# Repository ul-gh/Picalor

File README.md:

# Picalor

## Multi-Channel Heat Balance Calorimetry on the Raspberry Pi
--> Incomplete - work-in-progress! <--

Thermal power (or heat flow) measurement of one segmented or multiple
individual liquid-cooled or liquid-heated systems under the assumption
that the enthalpy difference of the fluid entering and exiting each system
per unit of time is equal to the energy dissipated or released by the system.

Quasi-isothermal condition can be achieved by using a sufficiently high
flow rate. Accurate heat flow measurements under these conditions
require very sensitive and robust differential temperature sensing.

This is implemented by the Picalor hardware using platinum resistive
temperature sensors in a deflection-type bridge configuration connected
to a multi-channel, high-precision delta-sigma ADC system.

When performing the measurement with fluid temperatures set nearly at
environmental temperature level, convection and radiation heat loss
can be made negligible e.g. for power loss measurements in electronics.

For applications in chemistry, the multi-channel hardware can be useful
for Constant Flux Calorimetry or segmented Continuous Reaction Calorimters.

Supported hardware:

* Picalor OSHW Raspberry Pi add-on circuit board featuring:
    - 16-channel analog frontend for Pt 1000 sensors
    - 4x pulse-timing flow sensor inputs
    - 2x ADS1256 24-Bit 8-ch ADC
* Waveshare "High Precision AD/DA board"

## Hardware:

* PCB Design Files: [picalor_hardware](picalor_hardware/)
* [Circuit Diagram (PDF)](https://ul-gh.github.io/Picalor/picalor_hardware/picalor_pcb.pdf)
* [Circuit BOM (HTML)](https://ul-gh.github.io/Picalor/picalor_hardware/ibom.html)

## Software Documentation (Generated):
* [Picalor Core (server component)](https://ul-gh.github.io/Picalor/picalor_core/html/namespaces.html)
* [Picalor App (browser client)](https://ul-gh.github.io/Picalor/picalor_app/html/files.html)

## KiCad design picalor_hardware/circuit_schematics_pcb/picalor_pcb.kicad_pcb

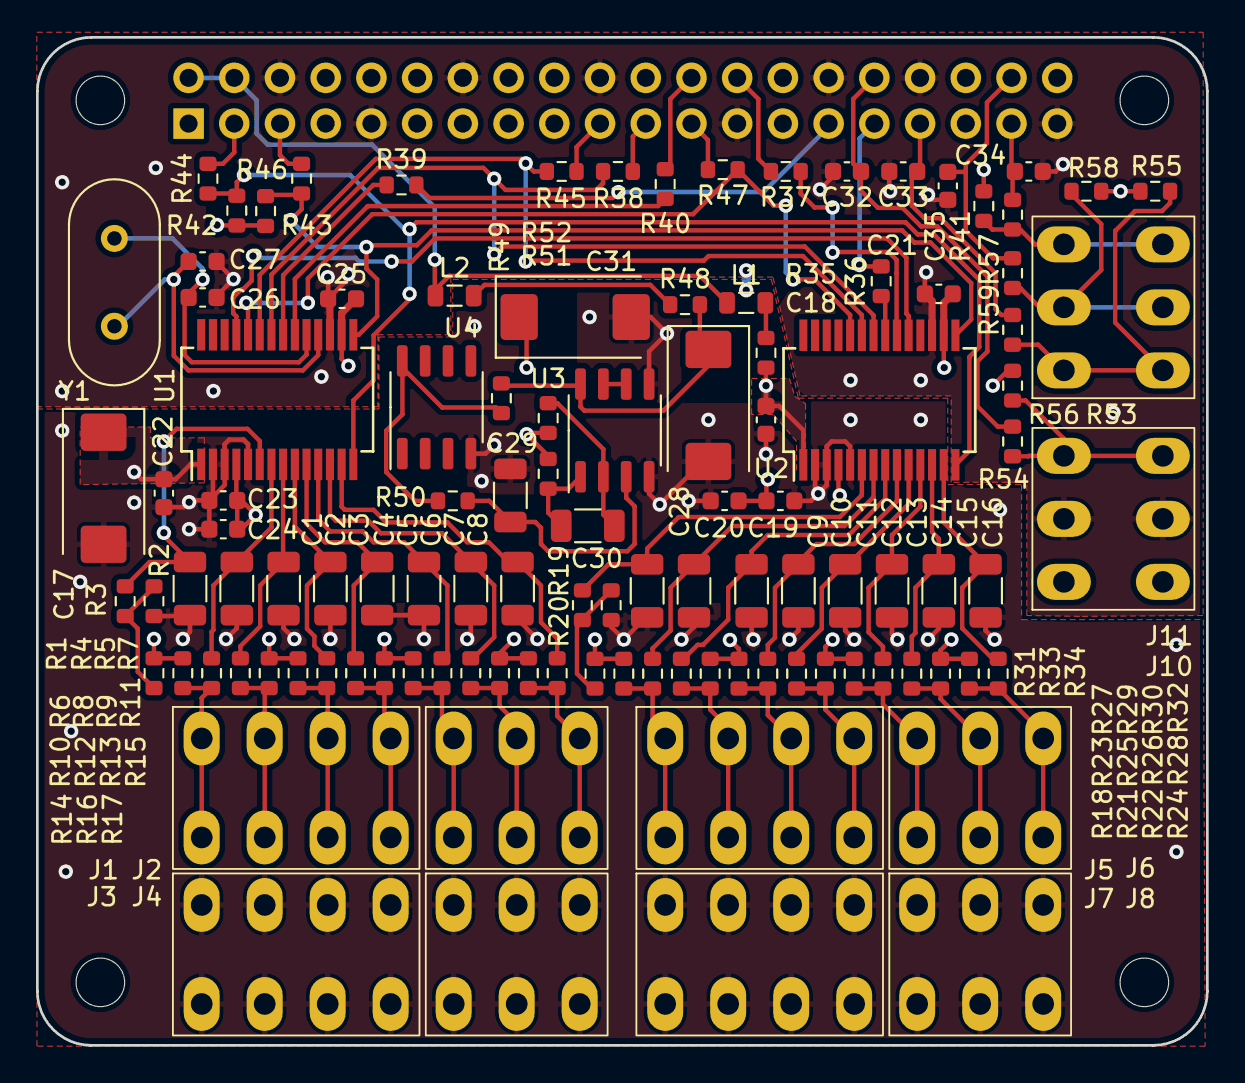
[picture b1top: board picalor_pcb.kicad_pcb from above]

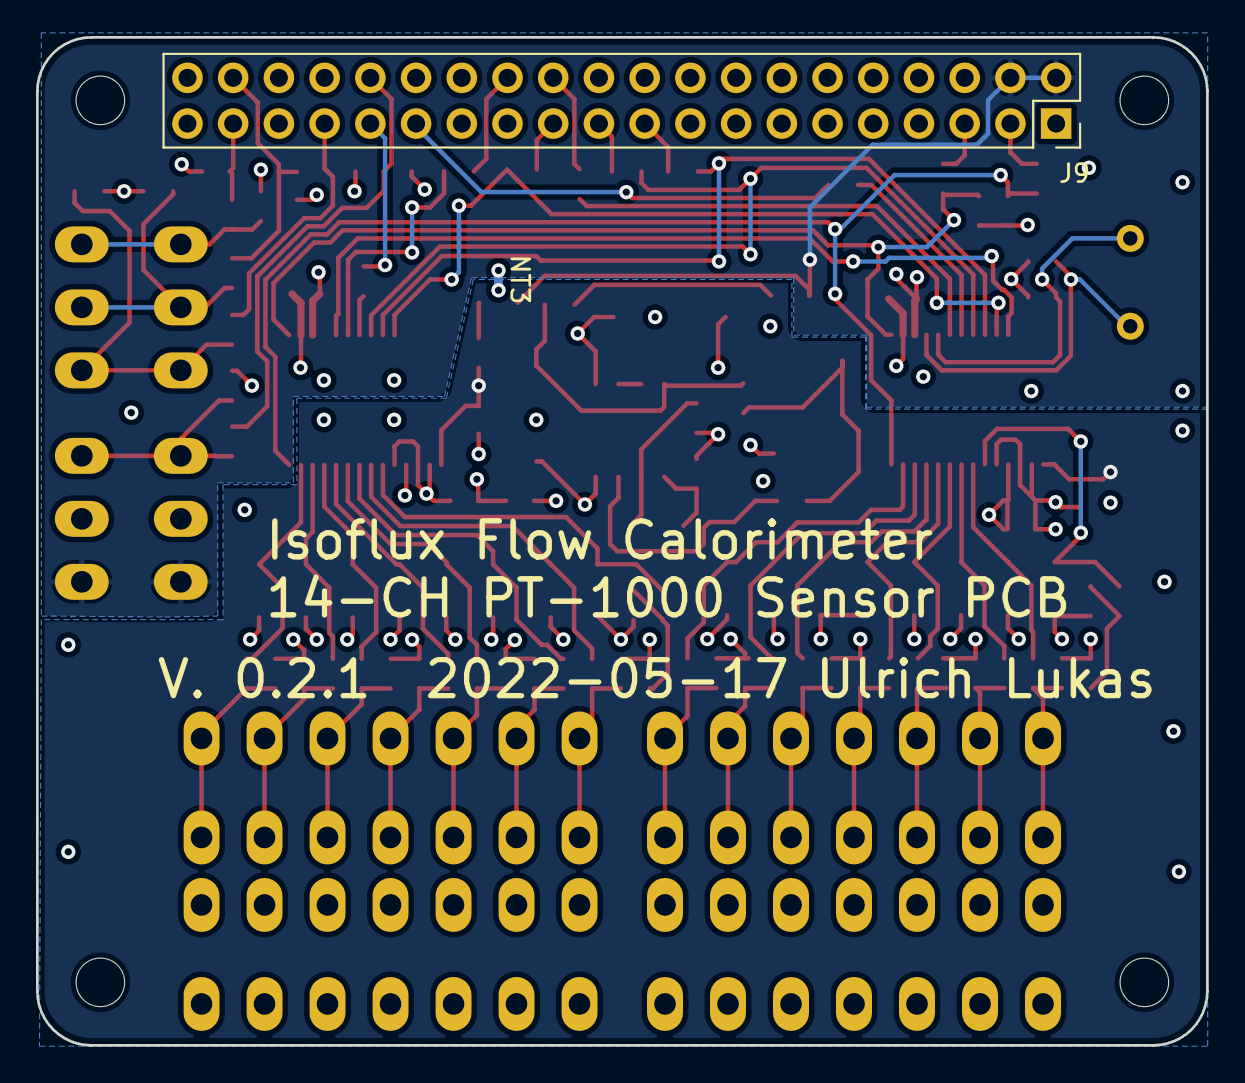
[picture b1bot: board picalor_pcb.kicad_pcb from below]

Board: 4 copper layers, 65.0 x 56.0 mm, 117 parts (2 on the bottom side), 75 nets.

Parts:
C1, C2, C3, C4, C5, C6, C7, C8, C9, C10, C11, C12, C13, C14, C15, C16, C29, C30: 1u; C_1206_3216Metric
C17, C28, C31: T491D 47U; CP_EIA-7343-31_Kemet-D
C18, C20, C21, C22, C24, C25: 100n; C_0603_1608Metric
C19, C23: 100p; C_0603_1608Metric
C26, C27: 47p; C_0603_1608Metric
C32, C33, C34, C35: 10n; C_0603_1608Metric
J1, J3, J5, J7: AST21304; TerminalBlock_MetzConnect_AST21304
J2, J4, J6, J8, J10, J11: AST21303; TerminalBlock_MetzConnect_AST21303
J9: Raspberry_Pi_2_3; PinSocket_2x20_P2.54mm_Vertical
L1, L2: BLM21AG102; L_0805_2012Metric
M1, M2, M3, M4: MountingHole_2.7mm_M2.5
NT3: NetTie_2; NetTie-2_SMD_Pad0.5mm
R1, R4, R6, R8, R10, R12, R14, R16, R18, R21, R23, R25, R27, R29, R31, R33, R42, R43, R50, R52: 10k; R_0603_1608Metric
R2, R3, R5, R7, R9, R11, R13, R15, R17, R19, R20, R22, R24, R26, R28, R30, R32, R34: 1k1; R_0603_1608Metric
R35, R48, R51: 10; R_0603_1608Metric
R36, R37, R38, R39, R40, R44, R45, R46, R47: 100; R_0603_1608Metric
R41, R49, R53, R55, R58: 2k2; R_0603_1608Metric
R54, R56, R57, R59: 220; R_0603_1608Metric
U1, U2: ADS1256IDB; SSOP-28_5.3x10.2mm_P0.65mm
U3: LM358; SO-8_3.9x4.9mm_P1.27mm
U4: LM336BM-2.5; SO-8_3.9x4.9mm_P1.27mm
Y1: 7.68M; Crystal_HC49-4H_Vertical

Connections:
2.5V_REF: C19.1, C20.1, C23.1, C24.1, C31.1, R1.1, R4.1, R6.1, R8.1, R10.1, R12.1, R14.1, R16.1, R18.1, R21.1, R23.1, R25.1, R27.1, R29.1, R31.1, R33.1, R51.2, R52.2, U1.4 (VREFP), U2.4 (VREFP)
3.3V_RPI: C21.1, C25.1, J9.1 (3V3), J9.17 (3V3), R41.1, R42.2, R43.2, R53.1, R55.1, R58.1, U1.16 (DVDD), U2.16 (DVDD)
5V_RPI: J9.2 (5V), J9.4 (5V), J10.1, L1.1, L2.1
/2x 24-Bit Delta-Sigma ADC/5V_FLT_ADC: C17.1, C18.1, C22.1, R35.2, U1.1 (AVDD), U2.1 (AVDD)
/2x 24-Bit Delta-Sigma ADC/ADC1_AIN0: C1.1, R3.2, U1.6 (AIN0)
/2x 24-Bit Delta-Sigma ADC/ADC1_AIN1: C2.1, R5.2, U1.7 (AIN1)
/2x 24-Bit Delta-Sigma ADC/ADC1_AIN2: C3.1, R7.2, U1.8 (AIN2)
/2x 24-Bit Delta-Sigma ADC/ADC1_AIN3: C4.1, R9.2, U1.9 (AIN3)
/2x 24-Bit Delta-Sigma ADC/ADC1_AIN4: C5.1, R11.2, U1.10 (AIN4)
/2x 24-Bit Delta-Sigma ADC/ADC1_AIN5: C6.1, R13.2, U1.11 (AIN5)
/2x 24-Bit Delta-Sigma ADC/ADC1_AIN6: C7.1, R15.2, U1.12 (AIN6)
/2x 24-Bit Delta-Sigma ADC/ADC1_AIN7: C8.1, R17.2, U1.13 (AIN7)
/2x 24-Bit Delta-Sigma ADC/ADC2_AIN0: C9.1, R20.2, U2.6 (AIN0)
/2x 24-Bit Delta-Sigma ADC/ADC2_AIN1: C10.1, R22.2, U2.7 (AIN1)
/2x 24-Bit Delta-Sigma ADC/ADC2_AIN2: C11.1, R24.2, U2.8 (AIN2)
/2x 24-Bit Delta-Sigma ADC/ADC2_AIN3: C12.1, R26.2, U2.9 (AIN3)
/2x 24-Bit Delta-Sigma ADC/ADC2_AIN4: C13.1, R28.2, U2.10 (AIN4)
/2x 24-Bit Delta-Sigma ADC/ADC2_AIN5: C14.1, R30.2, U2.11 (AIN5)
/2x 24-Bit Delta-Sigma ADC/ADC2_AIN6: C15.1, R32.2, U2.12 (AIN6)
/2x 24-Bit Delta-Sigma ADC/ADC2_AIN7: C16.1, R34.2, U2.13 (AIN7)
/2x 24-Bit Delta-Sigma ADC/CS1: J9.24 (~CE0/GPIO8), R40.2
/2x 24-Bit Delta-Sigma ADC/CS2: J9.26 (~CE1/GPIO7), R37.2
/2x 24-Bit Delta-Sigma ADC/DRDY1: J9.29 (GCLK1/GPIO5), R39.2
/2x 24-Bit Delta-Sigma ADC/DRDY2: J9.31 (GCLK2/GPIO6), R36.2
/2x 24-Bit Delta-Sigma ADC/MISO: J9.21 (MISO0/GPIO9), R38.2
/2x 24-Bit Delta-Sigma ADC/MOSI: J9.19 (MOSI0/GPIO10), R45.2
/2x 24-Bit Delta-Sigma ADC/SCK: J9.23 (SCLK0/GPIO11), R47.2
/2x 24-Bit Delta-Sigma ADC/~RESET: J9.5 (SCL/GPIO3), R46.2
/2x 24-Bit Delta-Sigma ADC/~SYNC_~PWDN: J9.3 (SDA/GPIO2), R44.2
/7x PT-1000 Sensor Bridge1/SNS_1A: J5.1, R21.2, R22.1
/7x PT-1000 Sensor Bridge1/SNS_2A: J5.2, R23.2, R24.1
/7x PT-1000 Sensor Bridge1/SNS_3A: J5.3, R25.2, R26.1
/7x PT-1000 Sensor Bridge1/SNS_4A: J5.4, R27.2, R28.1
/7x PT-1000 Sensor Bridge1/SNS_5A: J6.1, R29.2, R30.1
/7x PT-1000 Sensor Bridge1/SNS_6A: J6.2, R31.2, R32.1
/7x PT-1000 Sensor Bridge1/SNS_7A: J6.3, R33.2, R34.1
/7x PT-1000 Sensor Bridge/SNS_1A: J1.1, R4.2, R5.1
/7x PT-1000 Sensor Bridge/SNS_2A: J1.2, R6.2, R7.1
/7x PT-1000 Sensor Bridge/SNS_3A: J1.3, R8.2, R9.1
/7x PT-1000 Sensor Bridge/SNS_4A: J1.4, R10.2, R11.1
/7x PT-1000 Sensor Bridge/SNS_5A: J2.1, R12.2, R13.1
/7x PT-1000 Sensor Bridge/SNS_6A: J2.2, R14.2, R15.1
/7x PT-1000 Sensor Bridge/SNS_7A: J2.3, R16.2, R17.1
/Flow Sensors/FLOW_SNS_1: C32.1, J9.32 (PWM0/GPIO12), R54.1
/Flow Sensors/FLOW_SNS_2: C33.1, J9.33 (PWM1/GPIO13), R56.1
/Flow Sensors/FLOW_SNS_3: C34.1, J9.37 (GPIO26), R57.1
/Flow Sensors/FLOW_SNS_4: C35.1, J9.38 (GPIO20/MOSI1), R59.1
/Low 1_f Noise Reference Voltage Source/5V_FLT: C28.1, R48.2, R49.1, U3.8 (V+)
GNDA: C1.2, C2.2, C3.2, C4.2, C5.2, C6.2, C7.2, C8.2, C9.2, C10.2, C11.2, C12.2, C13.2, C14.2, C15.2, C16.2, C17.2, C18.2, C19.2, C20.2, C22.2, C23.2, C24.2, C28.2, C29.2, C31.2, J3.1, J3.2, J3.3, J3.4, J4.1, J4.2, J4.3, J7.1, J7.2, J7.3, J7.4, J8.1, J8.2, J8.3, NT3.2, R2.2, R19.2, U1.2 (AGND), U1.3 (VREFN), U1.5 (AINCOM), U2.2 (AGND), U2.3 (VREFN), U2.5 (AINCOM), U3.4 (V-), U3.5 (+), U4.4 (A)
GNDD: C21.2, C25.2, C26.1, C27.1, C32.2, C33.2, C34.2, C35.2, J9.6 (GND), J9.9 (GND), J9.14 (GND), J9.20 (GND), J9.25 (GND), J9.30 (GND), J9.34 (GND), J9.39 (GND), J10.2, NT3.1, U1.17 (DGND), U2.17 (DGND)
unnamed: C26.2, U1.19 (XTAL1_CLKIN), Y1.2
unnamed: C27.2, U1.18 (XTAL2), Y1.1
unnamed: C29.1, R50.2, U3.3 (+)
unnamed: C30.1, R51.1, U3.1
unnamed: C30.2, R52.1, U3.2 (-)
unnamed: J10.3, R53.2, R54.2
unnamed: J11.1, R55.2, R56.2
unnamed: J11.2, R58.2, R59.2
unnamed: J11.3, R41.2, R57.2
unnamed: L1.2, R35.1
unnamed: L2.2, R48.1
unnamed: R1.2, R2.1, R3.1
unnamed: R18.2, R19.1, R20.1
unnamed: R36.1, U2.21 (~DRDY)
unnamed: R37.1, U2.20 (~CS)
unnamed: R38.1, U1.22 (DOUT), U2.22 (DOUT)
unnamed: R39.1, U1.21 (~DRDY)
unnamed: R40.1, U1.20 (~CS)
unnamed: R42.1, R44.1, U1.14 (~SYNC_~PWDN), U2.14 (~SYNC_~PWDN)
unnamed: R43.1, R46.1, U1.15 (~RESET), U2.15 (~RESET)
unnamed: R45.1, U1.23 (DIN), U2.23 (DIN)
unnamed: R47.1, U1.24 (SCLK), U2.24 (SCLK)
unnamed: R49.2, R50.1, U4.8 (K)
unnamed: U1.25 (D0_CLKOUT), U2.19 (XTAL1_CLKIN)
unnamed: U3.6 (-), U3.7

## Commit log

2022-11-22 v0.1
2022-11-23 datalog
2022-11-23 toml_to_json
2022-11-23 remove unnecessary fonts CSS
2022-11-30 documentation
2022-12-02 docs
2022-12-10 hardware
2022-12-16 fix clear__datalog and tare__power
2022-12-16 fix clear__datalog
2023-01-03 Live Edit Table select input
2023-01-03 adc_calibration
2023-01-04 adc calibration api change
